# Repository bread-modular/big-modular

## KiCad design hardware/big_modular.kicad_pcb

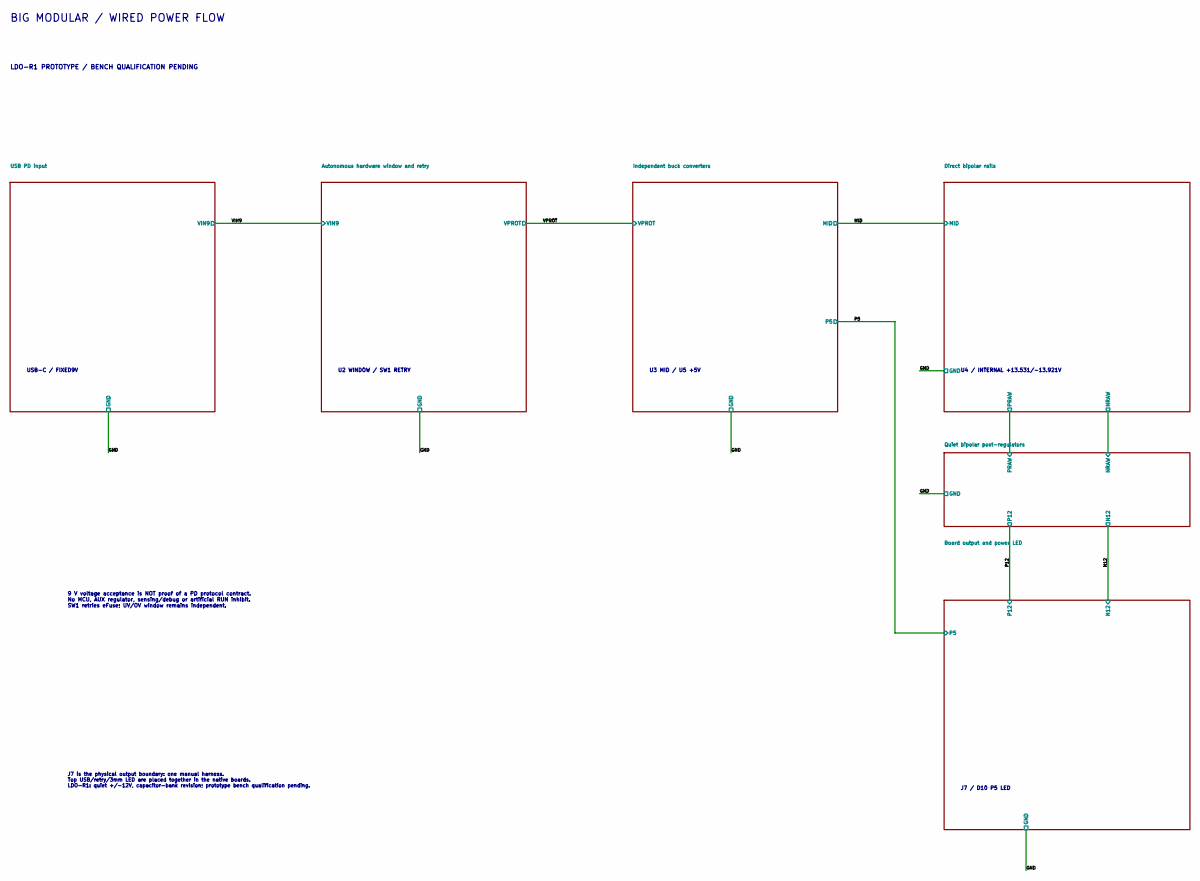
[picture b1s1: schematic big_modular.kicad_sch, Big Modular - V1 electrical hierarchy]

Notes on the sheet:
U4 / INTERNAL +13.531/-13.921V
BIG MODULAR / WIRED POWER FLOW
J7 is the physical output boundary: one manual harness. Top USB/retry/3mm LED are placed together in the native boards. LDO-R1: quiet +/-12V, capacitor-bank revision; prototype bench qualification pending.
9 V voltage acceptance is NOT proof of a PD protocol contract. No MCU, AUX regulator, sensing/debug or artificial RUN inhibit. SW1 retries eFuse; UV/OV window remains independent.
U2 WINDOW / SW1 RETRY
J7 / D10 P5 LED
LDO-R1 PROTOTYPE / BENCH QUALIFICATION PENDING
USB-C / FIXED9V
U3 MID / U5 +5V

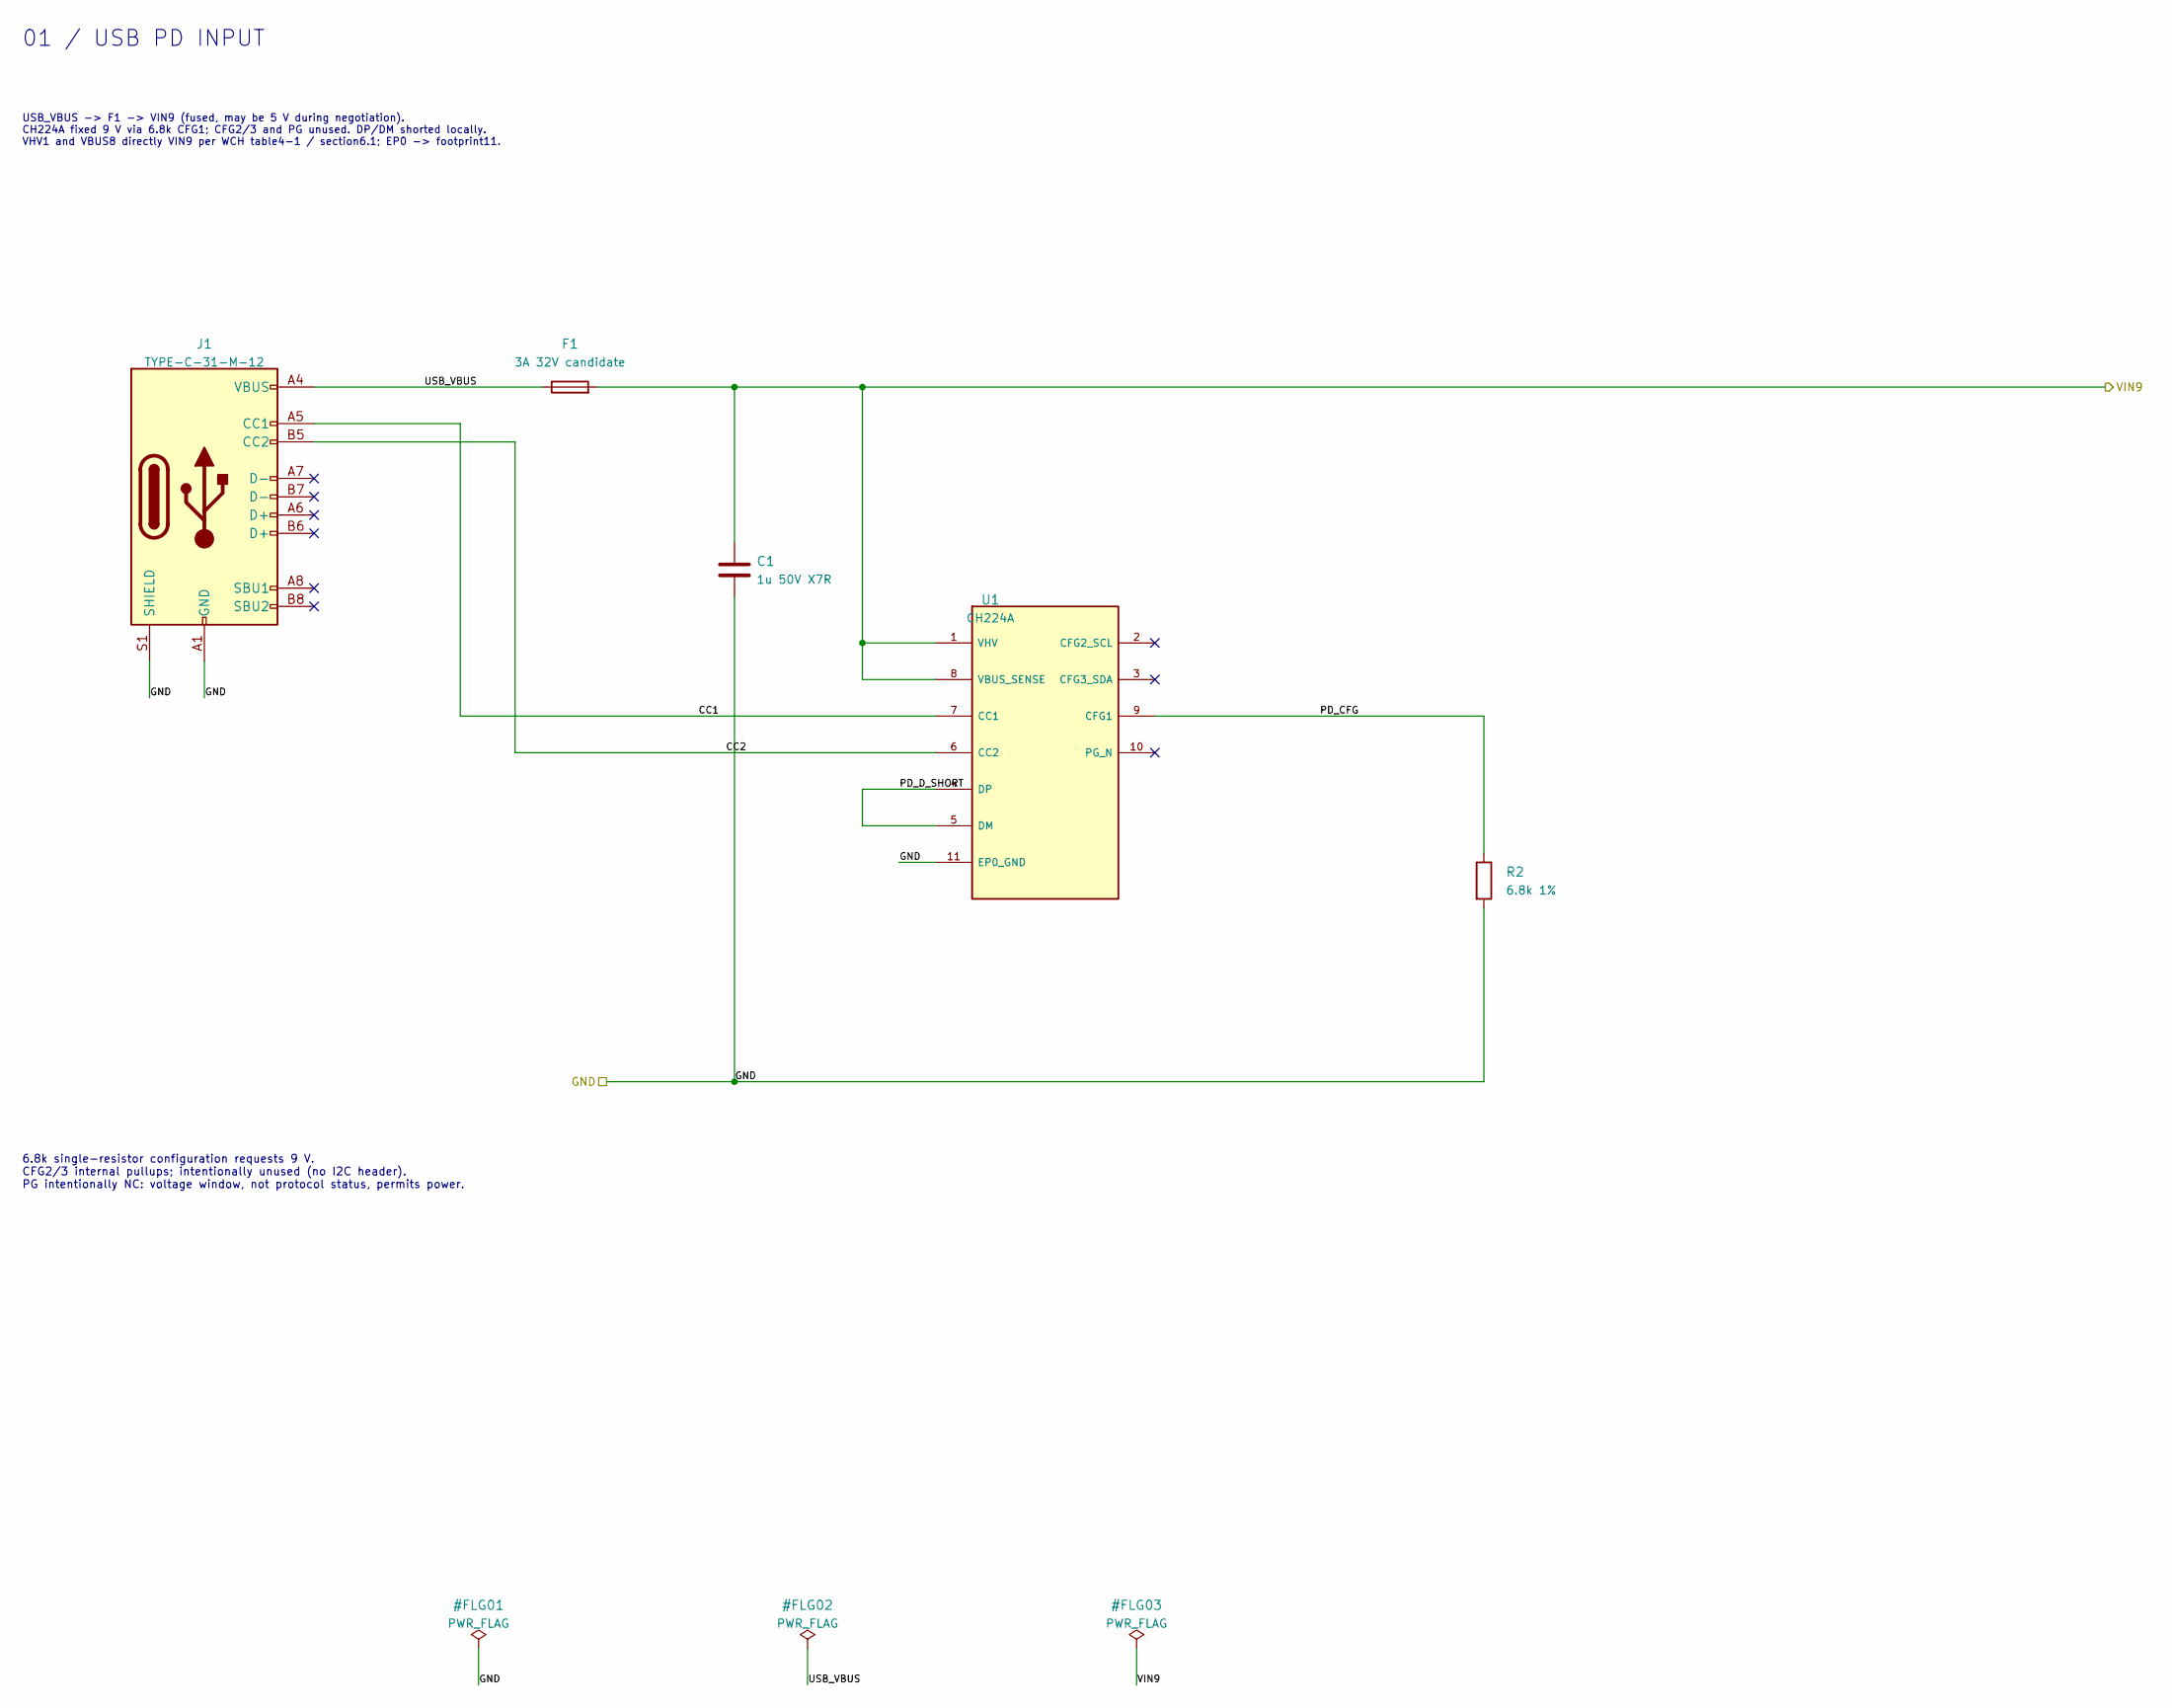
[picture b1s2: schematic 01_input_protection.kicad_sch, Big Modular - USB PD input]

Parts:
C1: 1u 50V X7R; C_0805_2012Metric; MPN CL21B105KBFNNNE; LCSC C28323
F1: 3A 32V candidate; Fuse_1206_3216Metric; MPN 0466003.NRHF; LCSC C14165
J1: TYPE-C-31-M-12; HRO-TYPE-C-31-M-12; MPN TYPE-C-31-M-12; LCSC C165948
R2: 6.8k 1%; R_0603_1608Metric; MPN 0603WAF6801T5E; LCSC C23212
U1: CH224A; SSOP-10-1EP_3.9x4.9mm_P1mm_EP2.1x3.3mm; MPN CH224A; LCSC C42459160

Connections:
/GND: C1.2, J1.A1 (GND), J1.A12 (GND), J1.S1 (SHIELD), R2.2, U1.11 (EP0_GND); also elsewhere on the board
/USB PD input/CC1: J1.A5 (CC1), U1.7 (CC1)
/USB PD input/CC2: J1.B5 (CC2), U1.6 (CC2)
/USB PD input/PD_CFG: R2.1, U1.9 (CFG1)
/USB PD input/PD_D_SHORT: U1.4 (DP), U1.5 (DM)
/USB PD input/USB_VBUS: F1.1, J1.A4 (VBUS), J1.A9 (VBUS)
/VIN9: C1.1, F1.2, U1.1 (VHV), U1.8 (VBUS_SENSE); also elsewhere on the board

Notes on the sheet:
01 / USB PD INPUT
6.8k single-resistor configuration requests 9 V. CFG2/3 internal pullups; intentionally unused (no I2C header). PG intentionally NC: voltage window, not protocol status, permits power.
USB_VBUS -> F1 -> VIN9 (fused, may be 5 V during negotiation). CH224A fixed 9 V via 6.8k CFG1; CFG2/3 and PG unused. DP/DM shorted locally. VHV1 and VBUS8 directly VIN9 per WCH table4-1 / section6.1; EP0 -> footprint11.

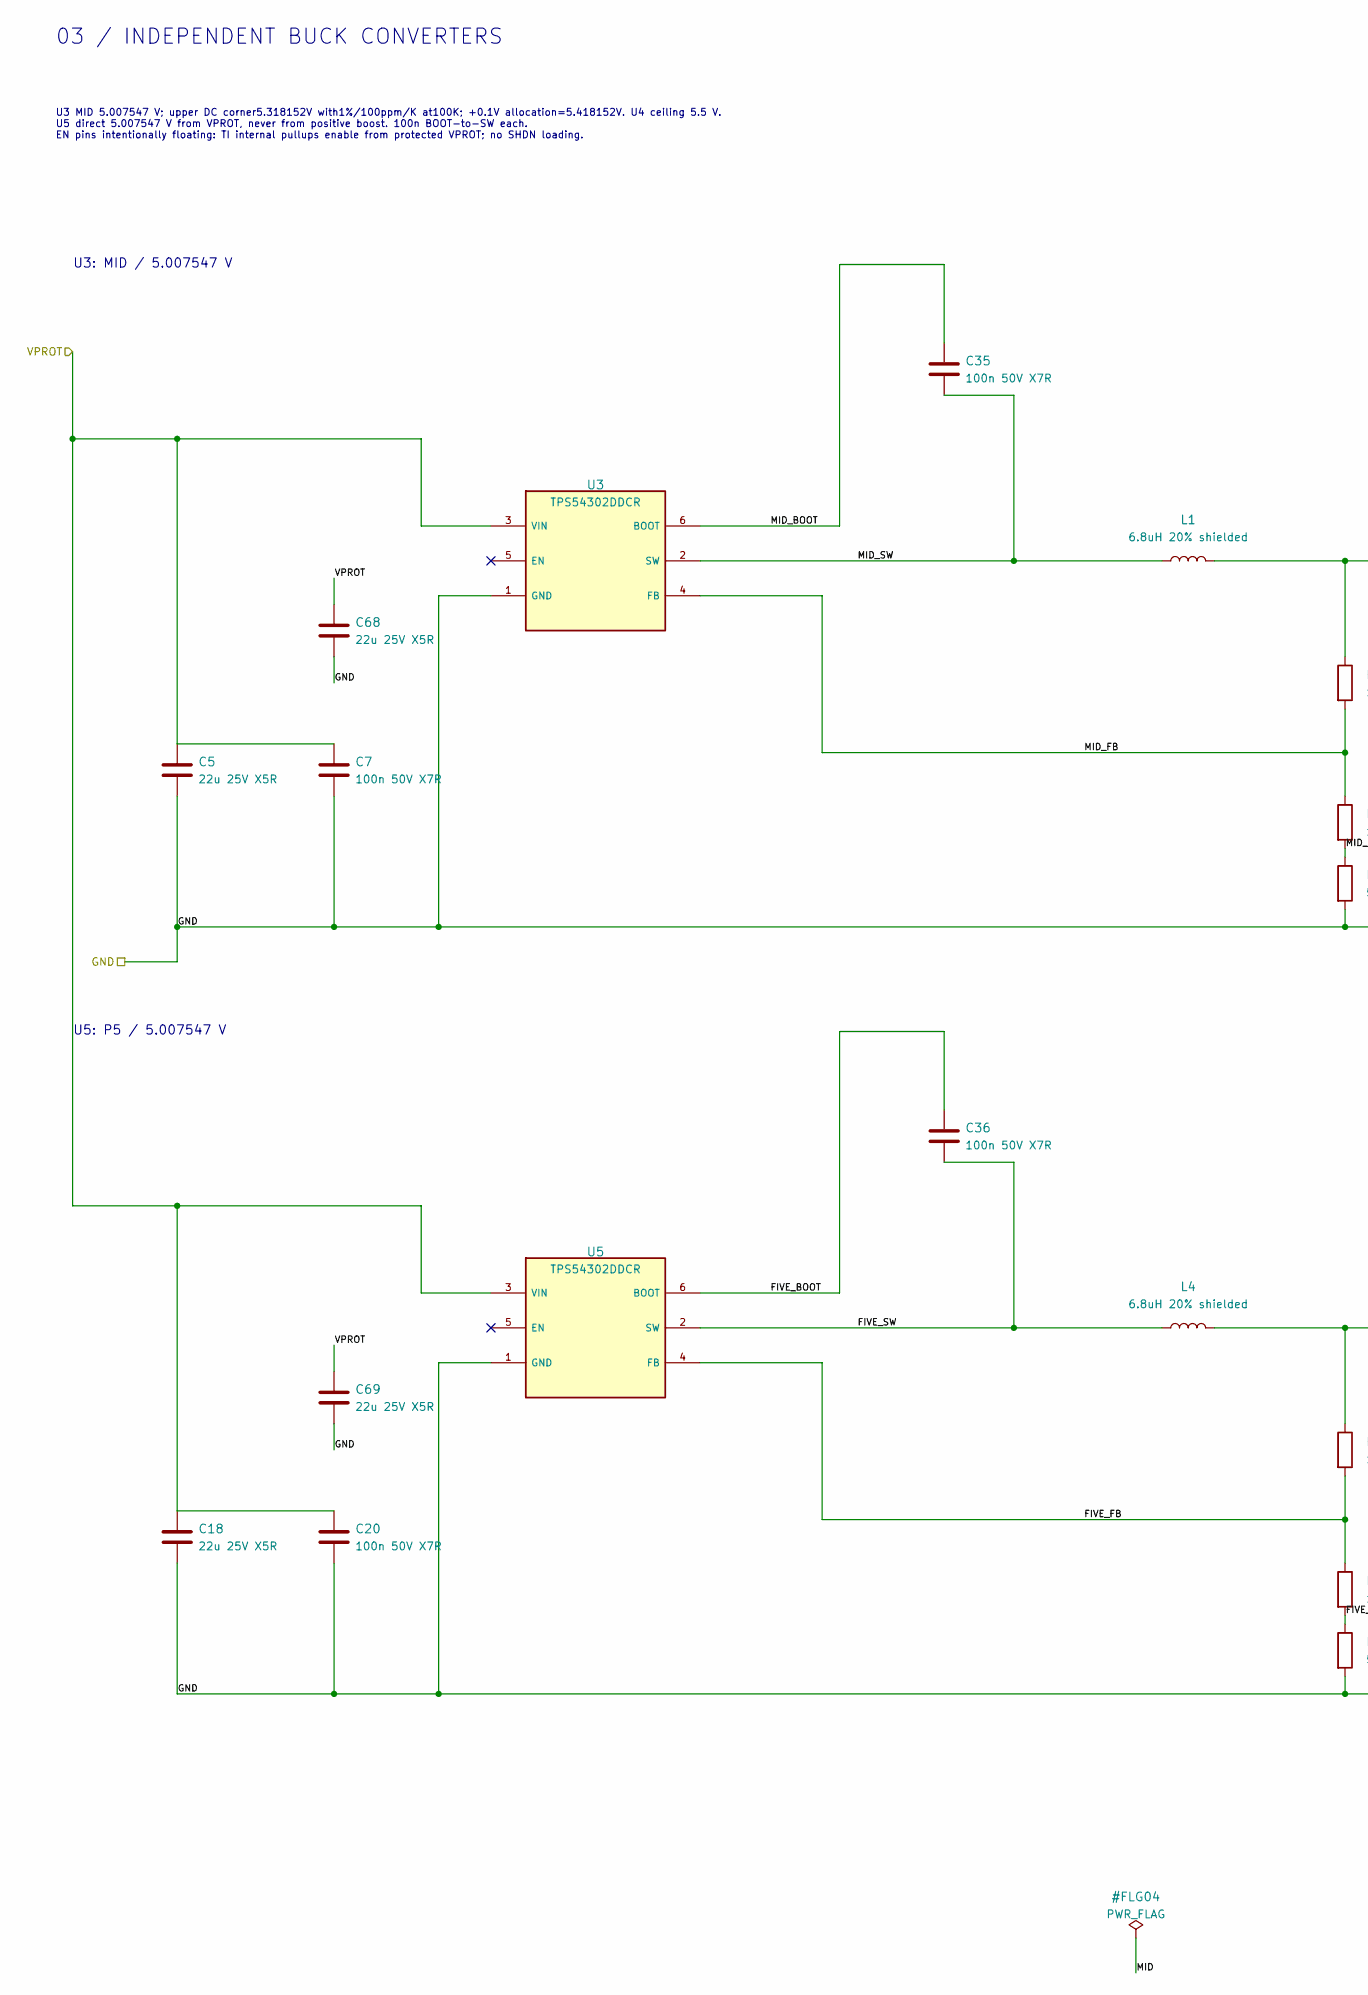
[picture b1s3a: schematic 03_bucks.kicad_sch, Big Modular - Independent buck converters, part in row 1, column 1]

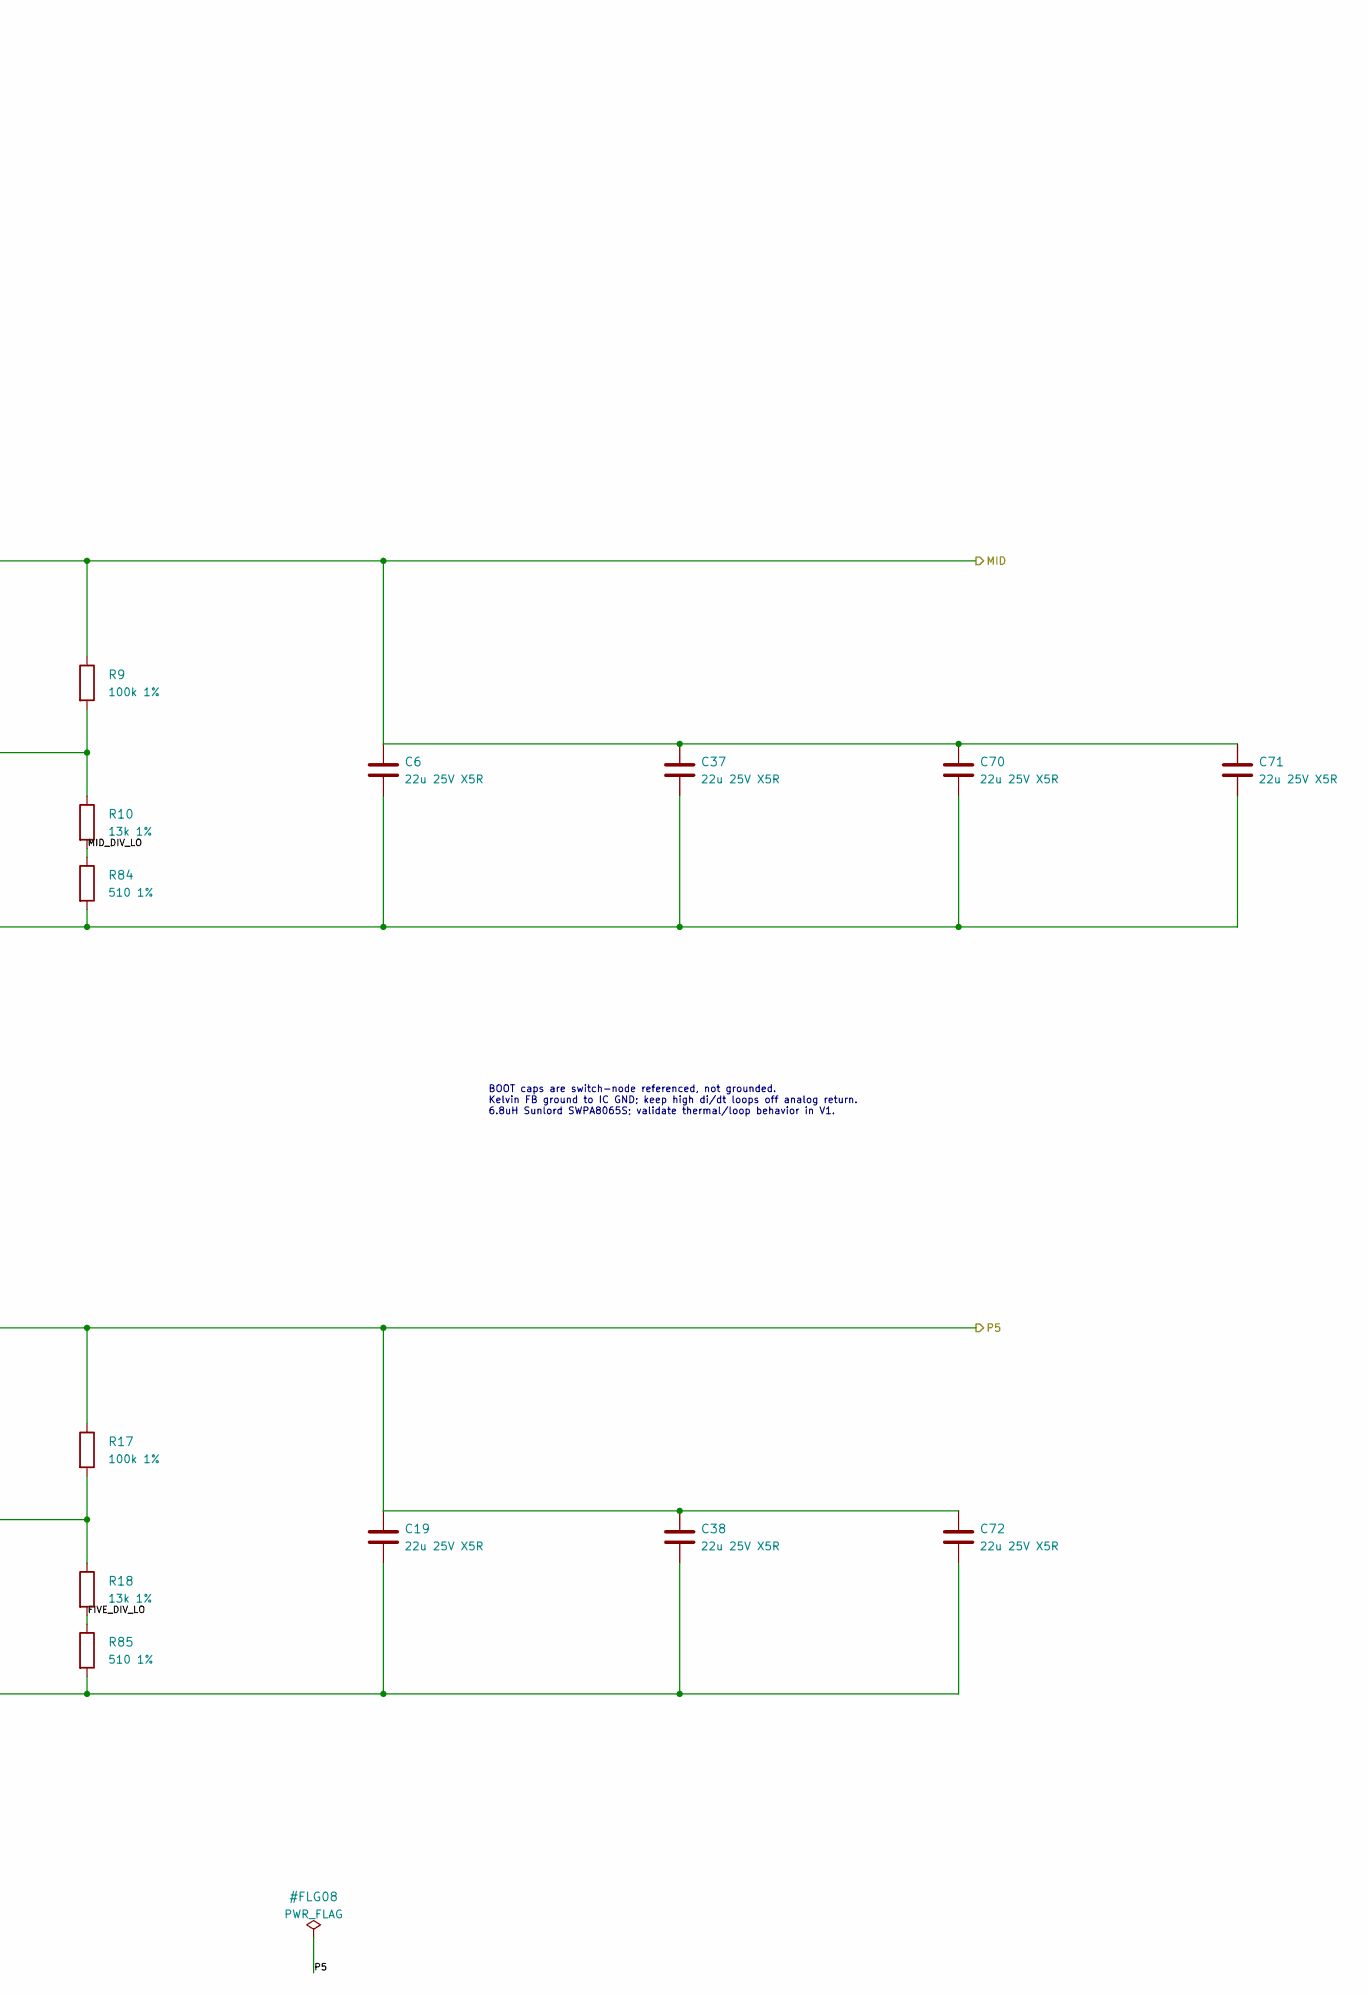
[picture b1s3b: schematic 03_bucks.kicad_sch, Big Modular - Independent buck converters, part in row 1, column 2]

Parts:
C5, C6, C18, C19, C37, C38, C68, C69, C70, C71, C72: 22u 25V X5R; C_1206_3216Metric; MPN CL31A226KAHNNNE; LCSC C12891
C7, C20, C35, C36: 100n 50V X7R; C_0603_1608Metric; MPN CC0603KRX7R9BB104; LCSC C14663
L1, L4: 6.8uH 20% shielded; L_KOHER_MDA1040; MPN MDA1040-6R8M; LCSC C2847552
R9, R17: 100k 1%; R_0603_1608Metric; MPN 0603WAF1003T5E; LCSC C25803
R10, R18: 13k 1%; R_0603_1608Metric; MPN 0603WAF1302T5E; LCSC C22797
R84, R85: 510 1%; R_0603_1608Metric; MPN 0603WAF5100T5E; LCSC C23193
U3, U5: TPS54302DDCR; SOT-23-6; MPN TPS54302DDCR; LCSC C311983

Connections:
/GND: C5.2, C6.2, C7.2, C18.2, C19.2, C20.2, C37.2, C38.2, C68.2, C69.2, C70.2, C71.2, C72.2, R84.2, R85.2, U3.1 (GND), U5.1 (GND); also elsewhere on the board
/Independent buck converters/FIVE_BOOT: C36.1, U5.6 (BOOT)
/Independent buck converters/FIVE_DIV_LO: R18.2, R85.1
/Independent buck converters/FIVE_FB: R17.2, R18.1, U5.4 (FB)
/Independent buck converters/FIVE_SW: C36.2, L4.1, U5.2 (SW)
/Independent buck converters/MID_BOOT: C35.1, U3.6 (BOOT)
/Independent buck converters/MID_DIV_LO: R10.2, R84.1
/Independent buck converters/MID_FB: R9.2, R10.1, U3.4 (FB)
/Independent buck converters/MID_SW: C35.2, L1.1, U3.2 (SW)
/MID: C6.1, C37.1, C70.1, C71.1, L1.2, R9.1; also elsewhere on the board
/P5: C19.1, C38.1, C72.1, L4.2, R17.1; also elsewhere on the board
/VPROT: C5.1, C7.1, C18.1, C20.1, C68.1, C69.1, U3.3 (VIN), U5.3 (VIN); also elsewhere on the board

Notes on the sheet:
U5: P5 / 5.007547 V
BOOT caps are switch-node referenced, not grounded. Kelvin FB ground to IC GND; keep high di/dt loops off analog return. 6.8uH Sunlord SWPA8065S; validate thermal/loop behavior in V1.
U3 MID 5.007547 V; upper DC corner5.318152V with1%/100ppm/K at100K; +0.1V allocation=5.418152V. U4 ceiling 5.5 V. U5 direct 5.007547 V from VPROT, never from positive boost. 100n BOOT-to-SW each. EN pins intentionally floating: TI internal pullups enable from protected VPROT; no SHDN loading.
U3: MID / 5.007547 V
03 / INDEPENDENT BUCK CONVERTERS

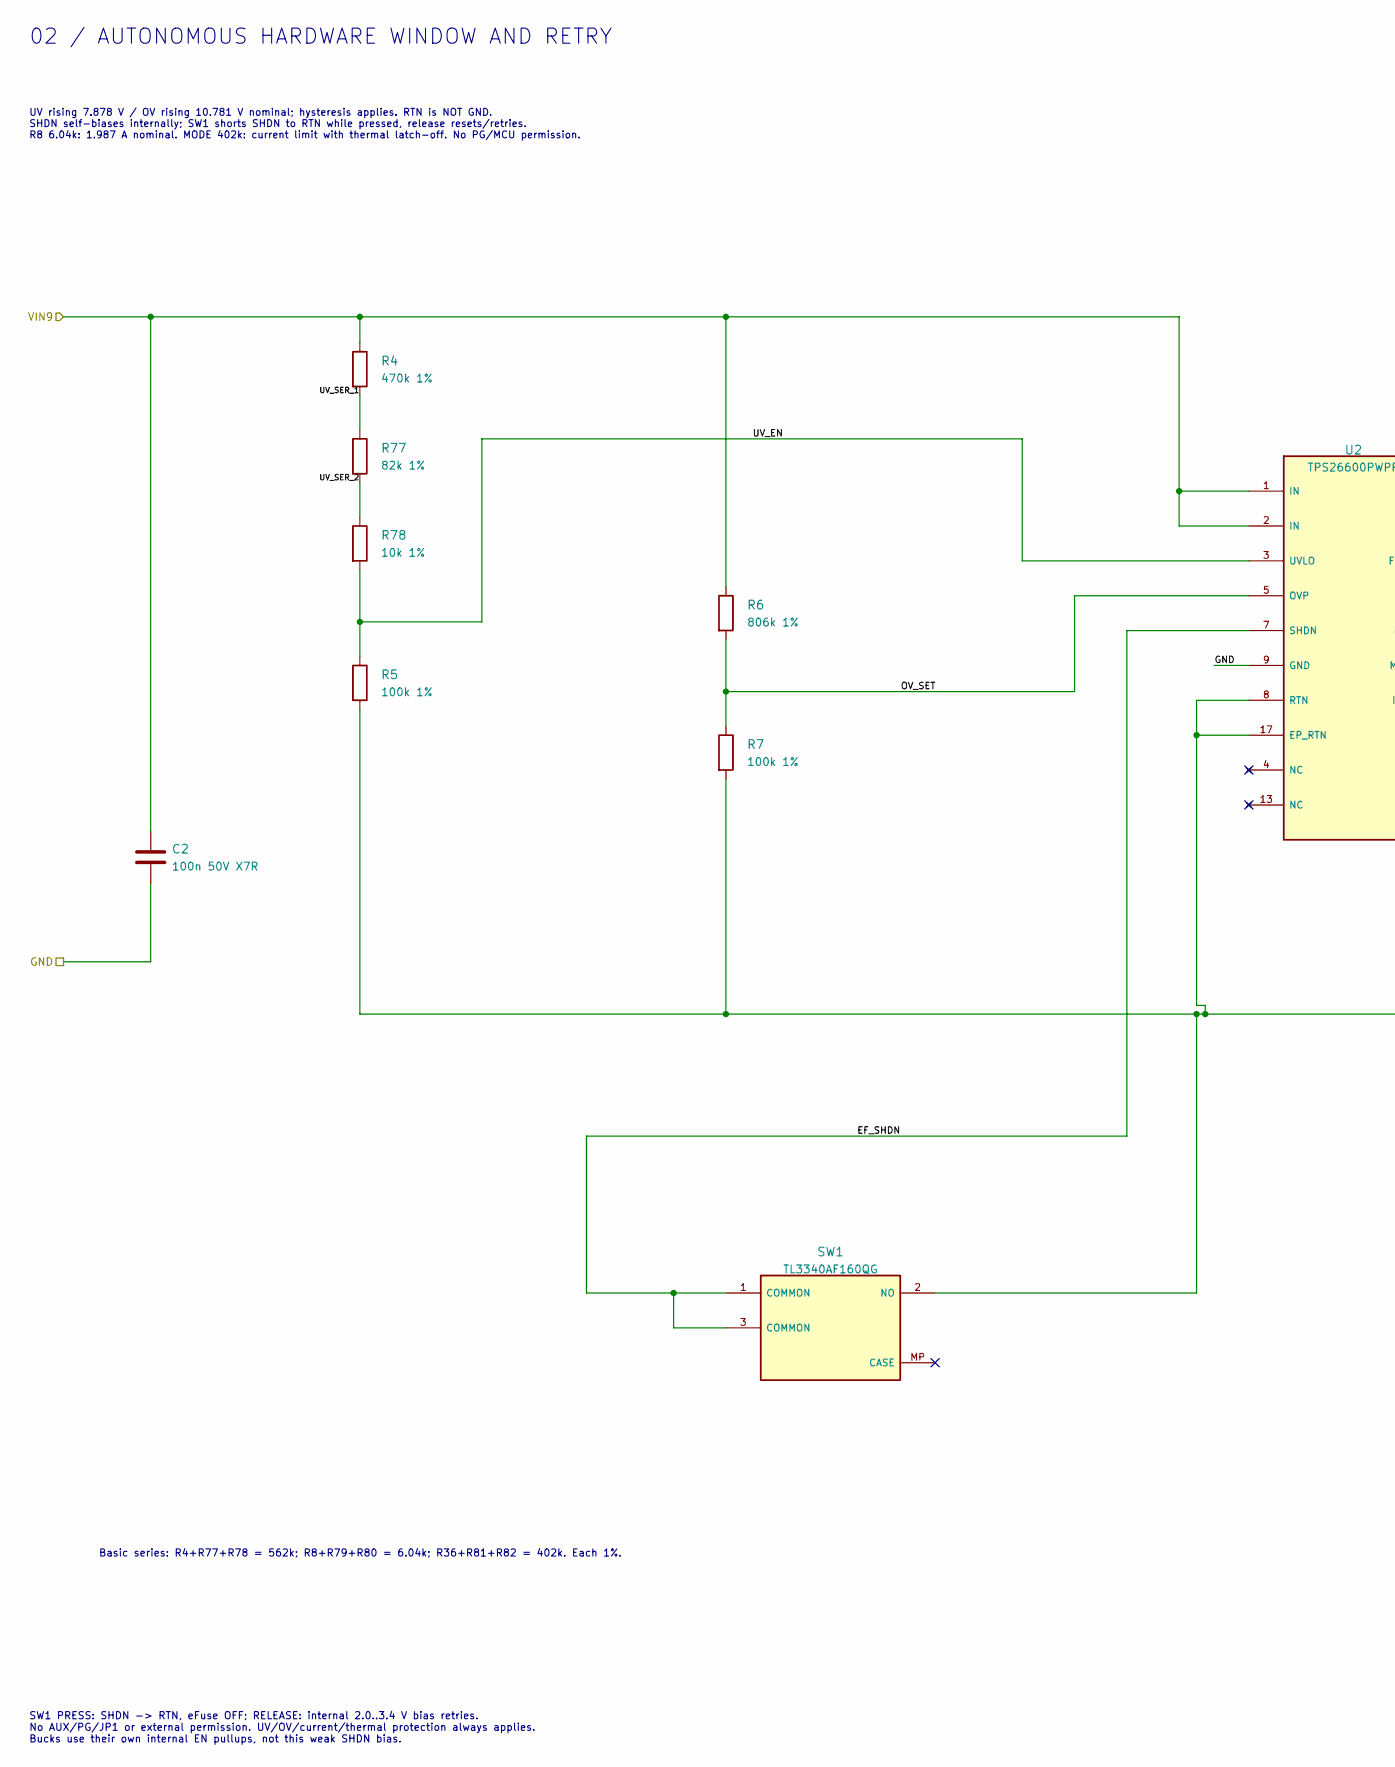
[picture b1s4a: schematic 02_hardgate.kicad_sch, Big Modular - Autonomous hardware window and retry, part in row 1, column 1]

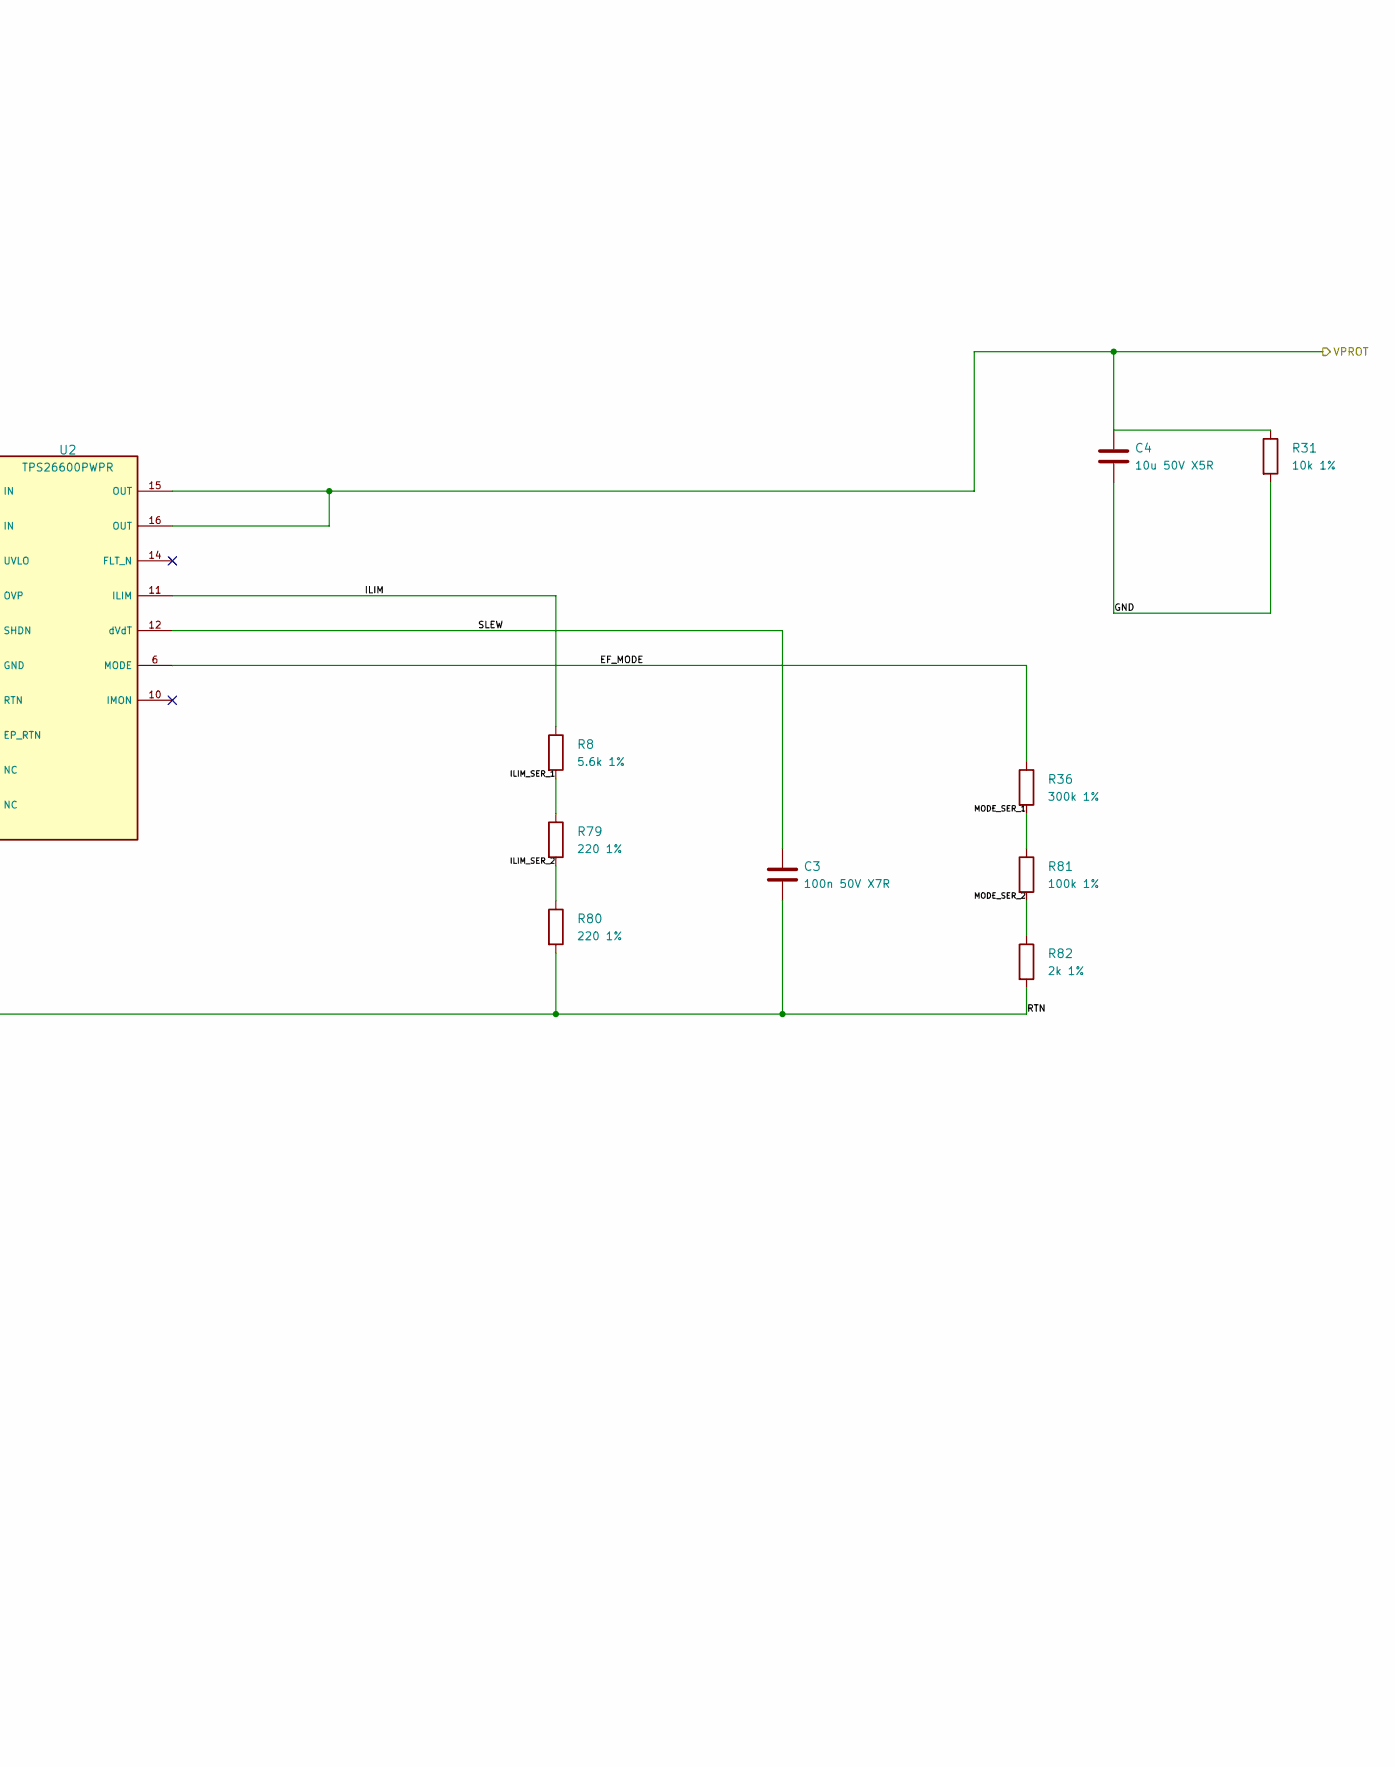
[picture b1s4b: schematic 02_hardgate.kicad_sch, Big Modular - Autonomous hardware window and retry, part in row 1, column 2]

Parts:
C2, C3: 100n 50V X7R; C_0603_1608Metric; MPN CC0603KRX7R9BB104; LCSC C14663
C4: 10u 50V X5R; C_1206_3216Metric; MPN CL31A106KBHNNNE; LCSC C13585
R4: 470k 1%; R_0603_1608Metric; MPN 0603WAF4703T5E; LCSC C23178
R5, R7, R81: 100k 1%; R_0603_1608Metric; MPN 0603WAF1003T5E; LCSC C25803
R6: 806k 1%; R_0603_1608Metric; MPN 0603WAF8063T5E; LCSC C23250
R8: 5.6k 1%; R_0603_1608Metric; MPN 0603WAF5601T5E; LCSC C23189
R31, R78: 10k 1%; R_0603_1608Metric; MPN 0603WAF1002T5E; LCSC C25804
R36: 300k 1%; R_0603_1608Metric; MPN 0603WAF3003T5E; LCSC C23024
R77: 82k 1%; R_0603_1608Metric; MPN 0603WAF8202T5E; LCSC C23254
R79, R80: 220 1%; R_0603_1608Metric; MPN 0603WAF2200T5E; LCSC C22962
R82: 2k 1%; R_0603_1608Metric; MPN 0603WAF2001T5E; LCSC C22975
SW1: TL3340AF160QG; SW_TL3340AF160QG_HandSolder; MPN TL3340AF160QG; LCSC C2886925
U2: TPS26600PWPR; HTSSOP-16-1EP_4.4x5mm_P0.65mm_EP3.4x5mm_Mask2.66x2.46mm; MPN TPS26600PWPR; LCSC C544399

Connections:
/Autonomous hardware window and retry/EF_MODE: R36.1, U2.6 (MODE)
/Autonomous hardware window and retry/EF_SHDN: SW1.1 (COMMON), SW1.3 (COMMON), U2.7 (SHDN)
/Autonomous hardware window and retry/ILIM: R8.1, U2.11 (ILIM)
/Autonomous hardware window and retry/ILIM_SER_1: R8.2, R79.1
/Autonomous hardware window and retry/ILIM_SER_2: R79.2, R80.1
/Autonomous hardware window and retry/MODE_SER_1: R36.2, R81.1
/Autonomous hardware window and retry/MODE_SER_2: R81.2, R82.1
/Autonomous hardware window and retry/OV_SET: R6.2, R7.1, U2.5 (OVP)
/Autonomous hardware window and retry/RTN: C3.2, R5.2, R7.2, R80.2, R82.2, SW1.2 (NO), U2.8 (RTN), U2.17 (EP_RTN)
/Autonomous hardware window and retry/SLEW: C3.1, U2.12 (dVdT)
/Autonomous hardware window and retry/UV_EN: R5.1, R78.2, U2.3 (UVLO)
/Autonomous hardware window and retry/UV_SER_1: R4.2, R77.1
/Autonomous hardware window and retry/UV_SER_2: R77.2, R78.1
/GND: C2.2, C4.2, R31.2, U2.9 (GND); also elsewhere on the board
/VIN9: C2.1, R4.1, R6.1, U2.1 (IN), U2.2 (IN); also elsewhere on the board
/VPROT: C4.1, R31.1, U2.15 (OUT), U2.16 (OUT); also elsewhere on the board

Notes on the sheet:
SW1 PRESS: SHDN -> RTN, eFuse OFF; RELEASE: internal 2.0..3.4 V bias retries. No AUX/PG/JP1 or external permission. UV/OV/current/thermal protection always applies. Bucks use their own internal EN pullups, not this weak SHDN bias.
02 / AUTONOMOUS HARDWARE WINDOW AND RETRY
UV rising 7.878 V / OV rising 10.781 V nominal; hysteresis applies. RTN is NOT GND. SHDN self-biases internally; SW1 shorts SHDN to RTN while pressed, release resets/retries. R8 6.04k: 1.987 A nominal. MODE 402k: current limit with thermal latch-off. No PG/MCU permission.
Basic series: R4+R77+R78 = 562k; R8+R79+R80 = 6.04k; R36+R81+R82 = 402k. Each 1%.

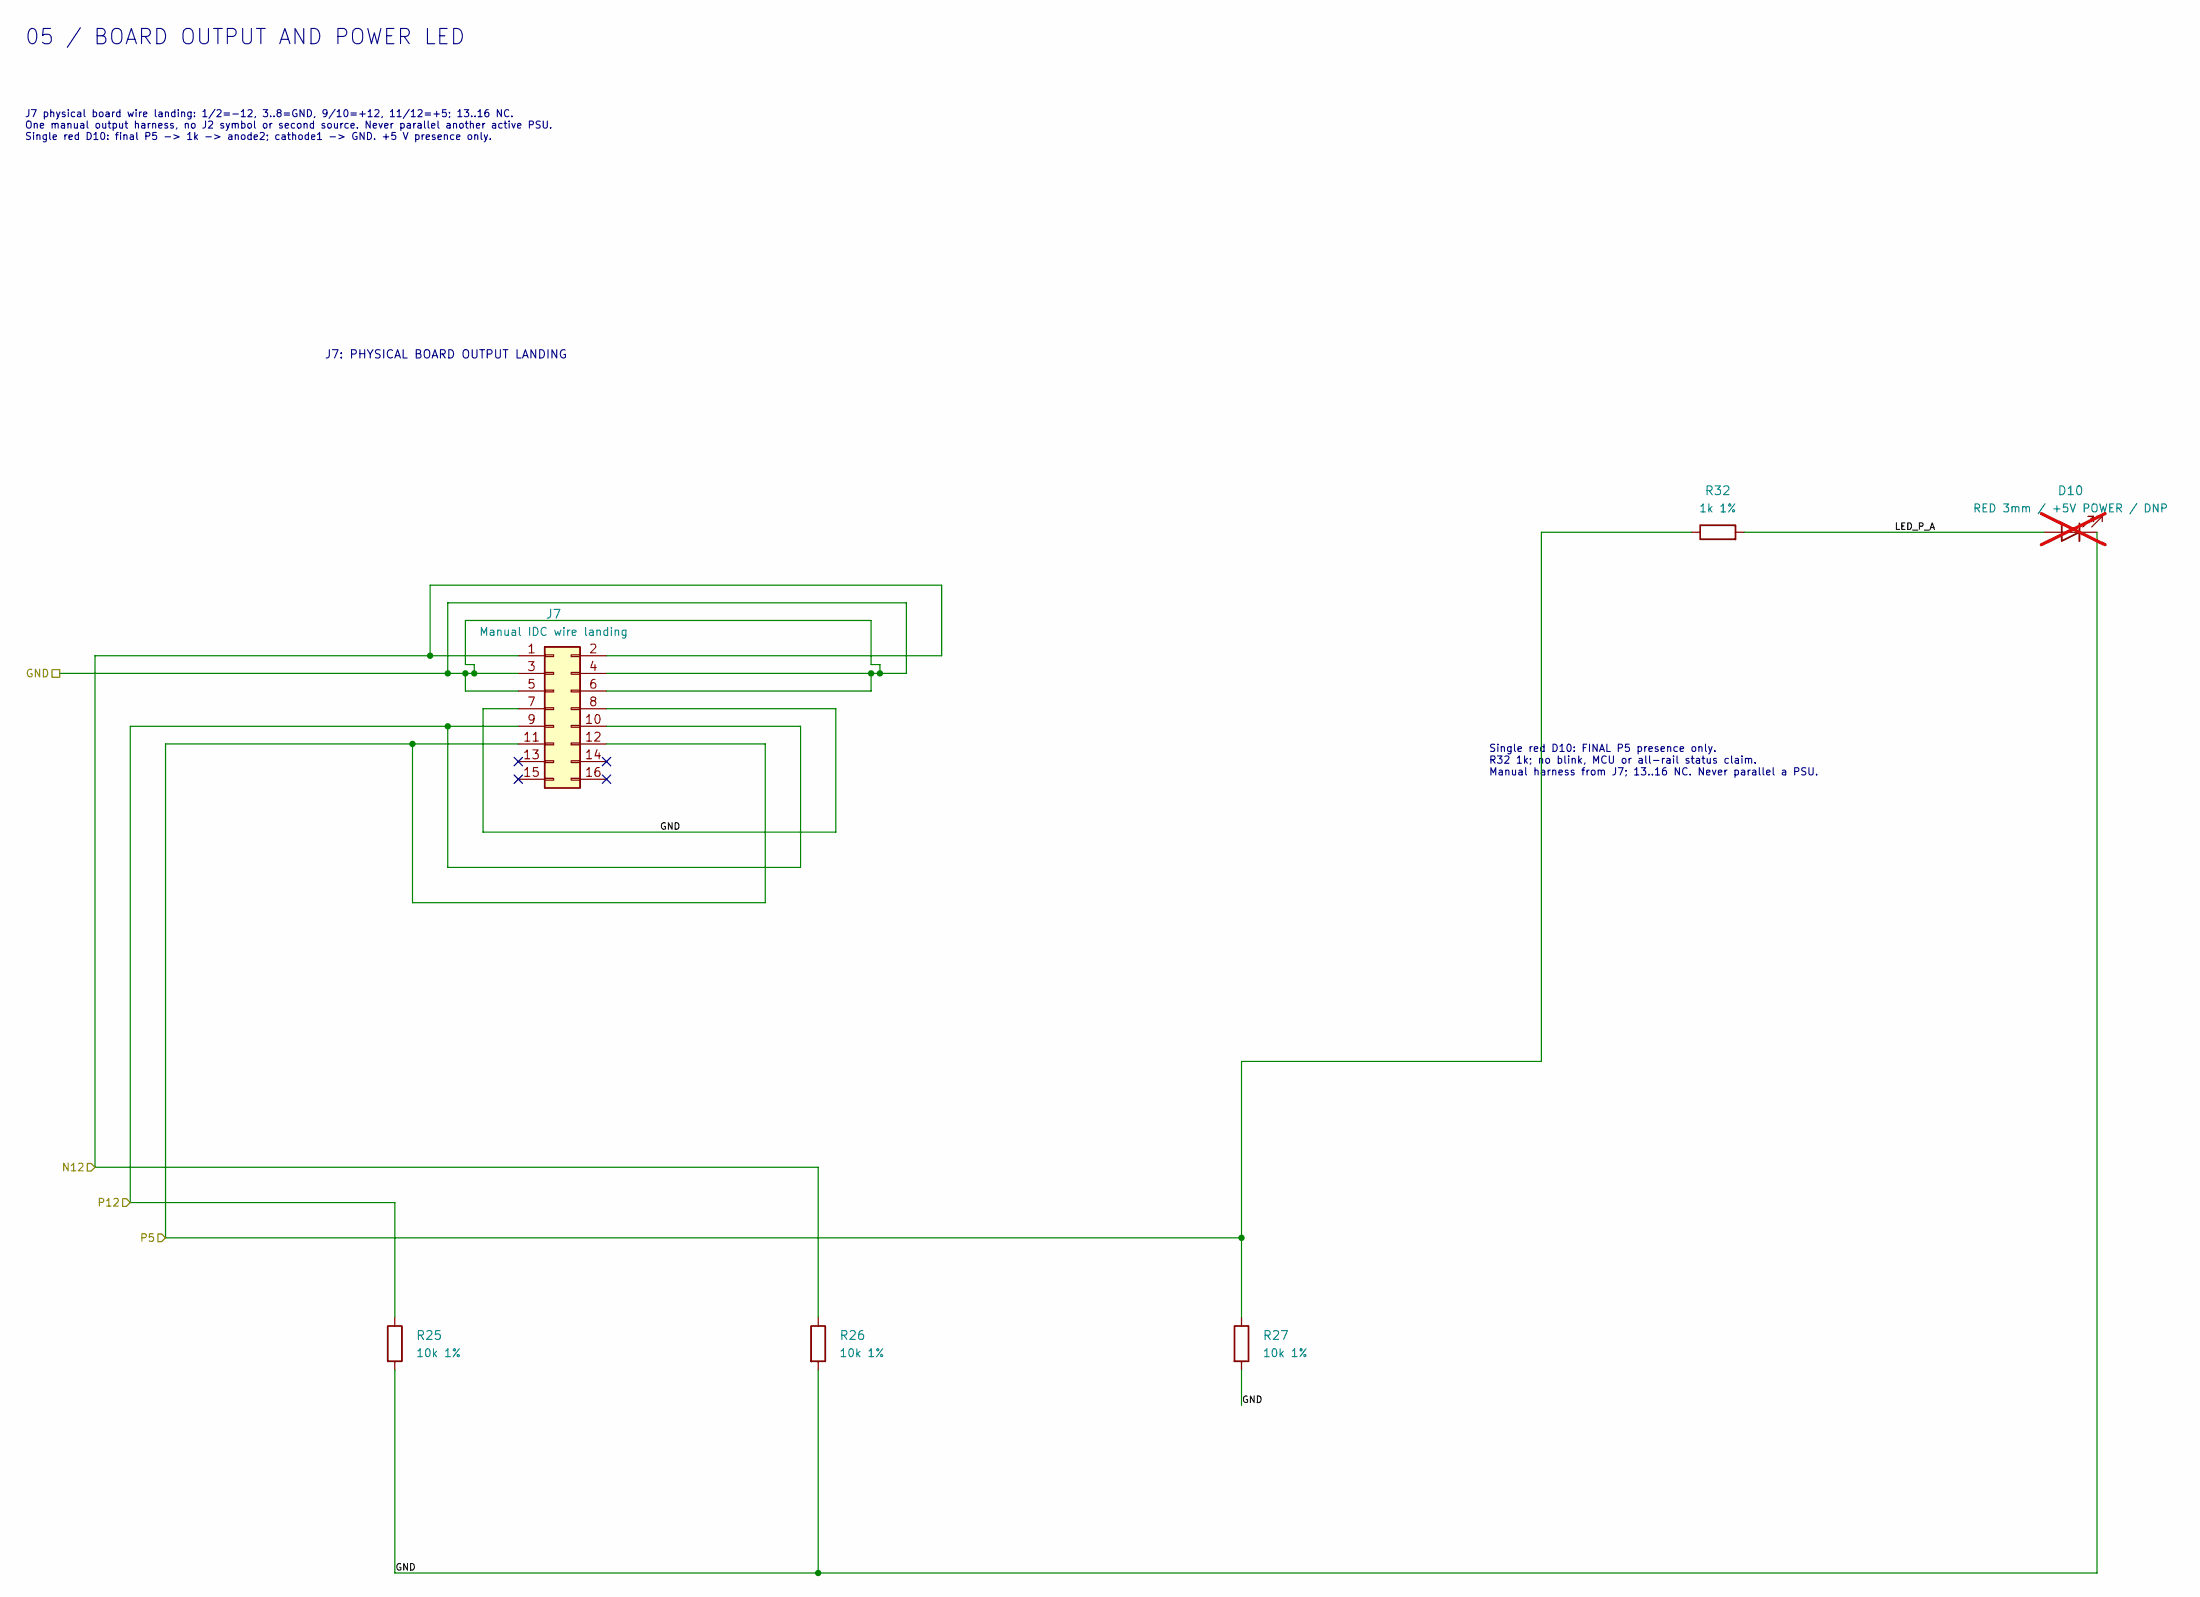
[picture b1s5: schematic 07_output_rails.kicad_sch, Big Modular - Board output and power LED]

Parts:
D10: RED 3mm / +5V POWER / DNP; LED_D3.0mm_Horizontal_O1.27mm_Z2.0mm_Edge; JLCPCB Exclude yes; not fitted
J7: Manual IDC wire landing; WireLanding_2x08_P2.54mm; JLCPCB Exclude yes
R25, R26, R27: 10k 1%; R_0603_1608Metric; MPN 0603WAF1002T5E; LCSC C25804
R32: 1k 1%; R_0603_1608Metric; MPN 0603WAF1001T5E; LCSC C21190

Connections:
/Board output and power LED/LED_P_A: D10.2 (A), R32.2
/GND: D10.1 (K), J7.3, J7.4, J7.5, J7.6, J7.7, J7.8, R25.2, R26.2, R27.2; also elsewhere on the board
/N12: J7.1, J7.2, R26.1; also elsewhere on the board
/P5: J7.11, J7.12, R27.1, R32.1; also elsewhere on the board
/P12: J7.9, J7.10, R25.1; also elsewhere on the board

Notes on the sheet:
Single red D10: FINAL P5 presence only. R32 1k; no blink, MCU or all-rail status claim. Manual harness from J7; 13..16 NC. Never parallel a PSU.
05 / BOARD OUTPUT AND POWER LED
J7: PHYSICAL BOARD OUTPUT LANDING
J7 physical board wire landing: 1/2=-12, 3..8=GND, 9/10=+12, 11/12=+5; 13..16 NC. One manual output harness, no J2 symbol or second source. Never parallel another active PSU. Single red D10: final P5 -> 1k -> anode2; cathode1 -> GND. +5 V presence only.
